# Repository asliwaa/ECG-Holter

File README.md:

# ECG Holter with MQTT Streaming

A portable ECG recorder that streams the signal in real time over Wi-Fi to a server using the MQTT protocol. The recorded signal is visualized live in a web dashboard.

Developed as an engineering thesis project in Computer Science at the Faculty of Automatic Control, Electronics and Computer Science, Silesian University of Technology (Politechnika Śląska).

---

## Table of contents

- [How it works](#how-it-works)
- [Hardware](#hardware)
- [Software](#software)
- [Repository structure](#repository-structure)
- [Project status](#project-status)
- [Safety](#safety)
- [License](#license)

---

## How it works

```mermaid
flowchart LR
    E[ECG electrodes] --> A[AD8232<br/>analog front-end]
    A -->|analog signal| M[ESP32-S3<br/>ADC, filtering, R-peak detection]
    M -->|Wi-Fi, MQTT| B[(Broker<br/>Mosquitto)]
    B -->|MQTT over WebSocket| D[Web dashboard<br/>live chart, BPM]
    P[Li-Po battery<br/>+ USB-C charging] -.-> M
    P -.-> A
```

1. The **AD8232** module amplifies and pre-filters the signal from the electrodes.
2. The **ESP32-S3** samples the signal with its ADC, applies digital filtering (high-pass and 50 Hz notch), detects R-peaks and calculates the heart rate.
3. Samples are sent in batches over **MQTT** to a Mosquitto broker.
4. The **web dashboard** subscribes to the data via MQTT over WebSocket and draws the ECG waveform live.

## Hardware

Custom PCB designed in KiCad 10, powered by a Li-Po battery.

| Block | Components | Function |
|---|---|---|
| USB-C input | GCT USB4105, USBLC6-2SC6 | Charging and programming, ESD protection |
| Charging | MCP73831 | Li-Po charging at 500 mA (CC/CV, 4.2 V) |
| Power path | AO3401A, SS14 | Automatic source selection: USB or battery |
| Regulator | AP2112K-3.3 | 3.3 V supply (up to 600 mA) |
| Microcontroller | ESP32-S3-WROOM-1-N8 | Acquisition, processing, Wi-Fi |
| ECG front-end | AD8232 module | ECG signal amplification and filtering, lead-off detection |
| Monitoring | Voltage dividers | Battery level, USB connection detection |

## Software

| Part | Technology |
|---|---|
| Firmware | ESP32-S3, Arduino / PlatformIO |
| Transport | MQTT |
| Broker | Mosquitto (with WebSocket support) |
| Dashboard | HTML / JavaScript, mqtt.js, real-time chart |

## Repository structure

```
├── hardware/        # KiCad project: schematic, PCB, libraries, fabrication files
├── firmware/        # ESP32-S3 firmware
├── server/          # Mosquitto broker configuration
├── dashboard/       # web dashboard
└── docs/            # documentation, photos, measurement results
```

## Project status

- [x] Concept and component selection
- [ ] Schematic (in progress)
- [ ] PCB layout and board order
- [ ] Breadboard prototype: ECG sampling
- [ ] MQTT streaming
- [ ] Web dashboard with live chart
- [ ] Bring-up of the custom PCB
- [ ] Digital filtering and heart rate detection
- [ ] Tests: latency, packet loss, battery life

## Safety

> [!WARNING]
> This is an educational prototype, **not a medical device**. It is not intended for diagnosis or health monitoring.
>
> When electrodes are attached to the body, the device must be powered **from the battery only**. Never attach electrodes while the board is connected via USB to a computer or a mains-powered charger. The firmware disables ECG acquisition when USB voltage is detected.

## License

- Software (`firmware/`, `server/`, `dashboard/`): [MIT](LICENSE)
- Hardware design (`hardware/`): [CERN-OHL-S-2.0](hardware/LICENSE)

## Author

Adam Śliwa · Engineering thesis

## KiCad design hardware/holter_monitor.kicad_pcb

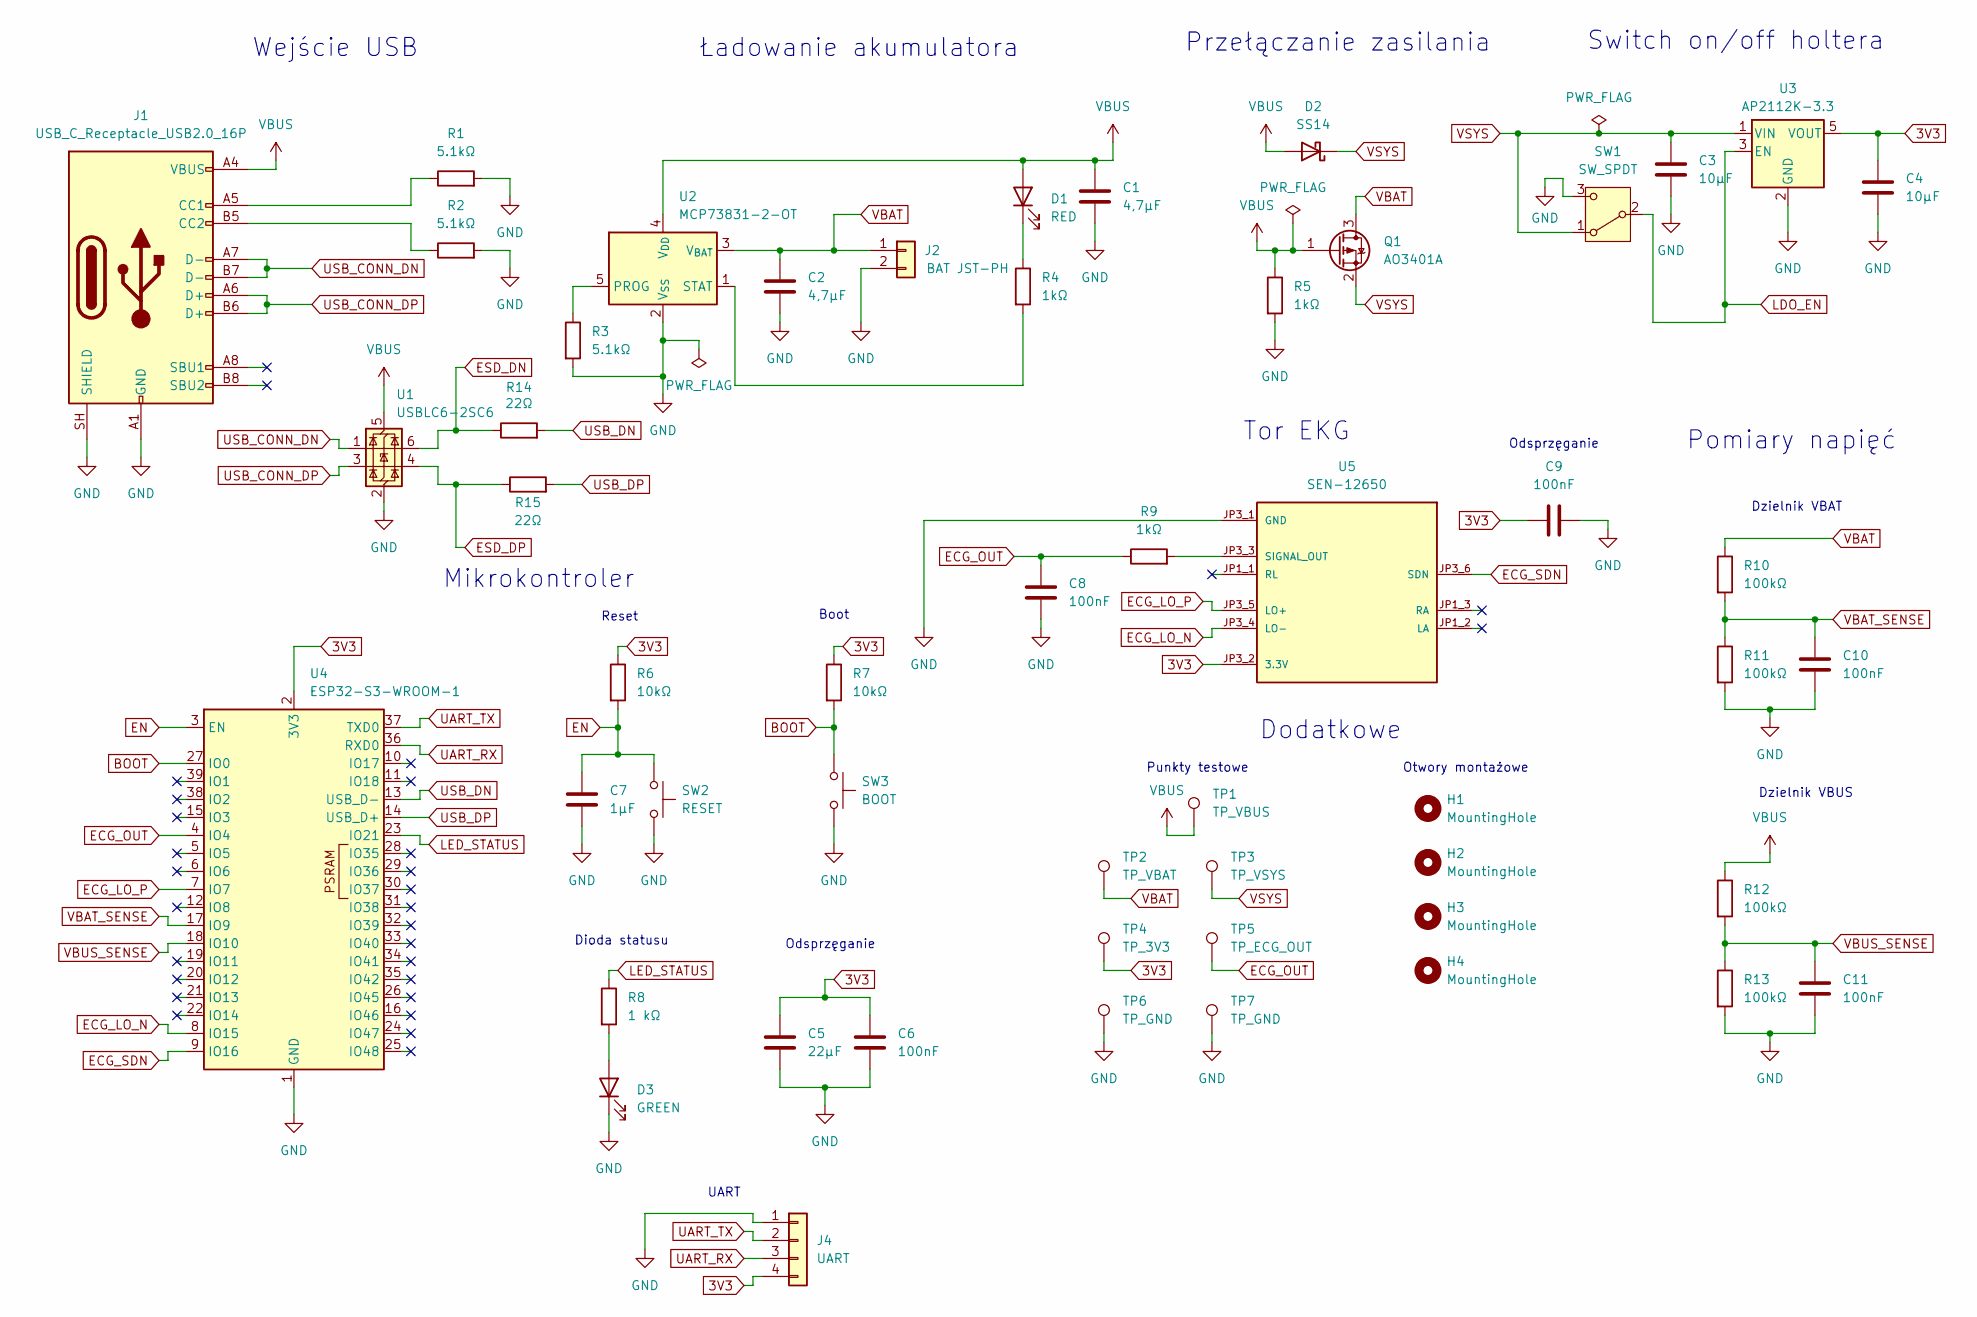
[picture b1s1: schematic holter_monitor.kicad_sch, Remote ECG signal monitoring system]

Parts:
C1, C2: 4,7µF; C_0805_2012Metric_Pad1.18x1.45mm_HandSolder
C3, C4: 10µF; C_0805_2012Metric_Pad1.18x1.45mm_HandSolder
C5: 22µF; C_0805_2012Metric_Pad1.18x1.45mm_HandSolder
C6, C8, C9, C10, C11: 100nF; C_0805_2012Metric_Pad1.18x1.45mm_HandSolder
C7: 1µF; C_0805_2012Metric_Pad1.18x1.45mm_HandSolder
D1: RED; LED_0805_2012Metric_Pad1.15x1.40mm_HandSolder
D2: SS14; D_SMA_Handsoldering
D3: GREEN; LED_0805_2012Metric_Pad1.15x1.40mm_HandSolder
H1, H2, H3, H4: MountingHole; MountingHole_3.2mm_M3
J1: USB_C_Receptacle_USB2.0_16P; USB_C_Receptacle_GCT_USB4105-xx-A_16P_TopMnt_Horizontal
J2: BAT JST-PH; JST_PH_S2B-PH-K_1x02_P2.00mm_Horizontal
J4: UART; PinHeader_1x04_P2.54mm_Vertical
Q1: AO3401A; SOT-23_Handsoldering
R1, R2, R3: 5.1kΩ; R_0805_2012Metric_Pad1.20x1.40mm_HandSolder
R4, R5, R9: 1kΩ; R_0805_2012Metric_Pad1.20x1.40mm_HandSolder
R6, R7: 10kΩ; R_0805_2012Metric_Pad1.20x1.40mm_HandSolder
R8: 1 kΩ; R_0805_2012Metric_Pad1.20x1.40mm_HandSolder
R10, R11, R12, R13: 100kΩ; R_0805_2012Metric_Pad1.20x1.40mm_HandSolder
R14, R15: 22Ω; R_0805_2012Metric_Pad1.20x1.40mm_HandSolder
SW1: SW_SPDT; SW_Slide_SPDT_Straight_CK_OS102011MS2Q
SW2: RESET; SW_SPST_TL3342
SW3: BOOT; SW_SPST_TL3342
TP1: TP_VBUS; TestPoint_Pad_D1.5mm
TP2: TP_VBAT; TestPoint_Pad_D1.5mm
TP3: TP_VSYS; TestPoint_Pad_D1.5mm
TP4: TP_3V3; TestPoint_Pad_D1.5mm
TP5: TP_ECG_OUT; TestPoint_Pad_D1.5mm
TP6, TP7: TP_GND; TestPoint_Pad_D1.5mm
U1: USBLC6-2SC6; SOT-23-6_Handsoldering
U2: MCP73831-2-OT; SOT-23-5_HandSoldering
U3: AP2112K-3.3; SOT-23-5_HandSoldering
U4: ESP32-S3-WROOM-1
U5: SEN-12650; MODULE_SEN-12650; PARTREV V10

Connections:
3V3: C4.1, C5.1, C6.1, C9.1, J4.4, R6.1, R7.1, TP4.1 (1_1), U3.5 (VOUT), U4.2 (3V3), U5.JP3_2 (3.3V)
BOOT: R7.2, SW3.1, U4.27 (IO0)
ECG_LO_N: U4.8 (IO15), U5.JP3_4 (LO-)
ECG_LO_P: U4.7 (IO7), U5.JP3_5 (LO+)
ECG_OUT: C8.1, R9.1, TP5.1 (1_1), U4.4 (IO4)
ECG_SDN: U4.9 (IO16), U5.JP3_6 (SDN)
EN: C7.1, R6.2, SW2.1, U4.3 (EN)
ESD_DN: R14.1, U1.6 (I/O1)
ESD_DP: R15.1, U1.4 (I/O2)
GND: C1.2, C2.2, C3.2, C4.2, C5.2, C6.2, C7.2, C8.2, C9.2, C10.2, C11.2, D3.1 (K), J1.A1 (GND), J1.A12 (GND), J1.B1 (GND), J1.B12 (GND), J1.SH (SHIELD), J2.2, J4.1, R1.2, R2.2, R3.2, R5.2, R11.2, R13.2, SW1.3 (C), SW2.2, SW3.2, TP6.1 (1_1), TP7.1 (1_1), U1.2 (GND), U2.2 (V_{SS}), U3.2 (GND), U4.1 (GND), U4.40 (GND), U4.41 (GND), U5.JP3_1 (GND)
LDO_EN: SW1.2 (B), U3.3 (EN)
LED_STATUS: R8.1, U4.23 (IO21)
unnamed: D1.1 (K), R4.1
unnamed: D3.2 (A), R8.2
unnamed: J1.A5 (CC1), R1.1
unnamed: J1.B5 (CC2), R2.1
unnamed: R3.1, U2.5 (PROG)
unnamed: R4.2, U2.1 (STAT)
unnamed: R9.2, U5.JP3_3 (SIGNAL_OUT)
UART_RX: J4.3, U4.36 (RXD0)
UART_TX: J4.2, U4.37 (TXD0)
USB_CONN_DN: J1.A7 (D-), J1.B7 (D-), U1.1 (I/O1)
USB_CONN_DP: J1.A6 (D+), J1.B6 (D+), U1.3 (I/O2)
USB_DN: R14.2, U4.13 (USB_D-)
USB_DP: R15.2, U4.14 (USB_D+)
VBAT: C2.1, J2.1, Q1.3 (D), R10.1, TP2.1 (1_1), U2.3 (V_{BAT})
VBAT_SENSE: C10.1, R10.2, R11.1, U4.17 (IO9)
VBUS: C1.1, D1.2 (A), D2.2 (A), J1.A4 (VBUS), J1.A9 (VBUS), J1.B4 (VBUS), J1.B9 (VBUS), Q1.1 (G), R5.1, R12.1, TP1.1 (1_1), U1.5 (VBUS), U2.4 (V_{DD})
VBUS_SENSE: C11.1, R12.2, R13.1, U4.18 (IO10)
VSYS: C3.1, D2.1 (K), Q1.2 (S), SW1.1 (A), TP3.1 (1_1), U3.1 (VIN)

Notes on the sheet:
Dzielnik VBAT
Boot
Reset
Odsprzęganie
Switch on/off holtera
UART
Przełączanie zasilania
Wejście USB
Dzielnik VBUS
Dioda statusu
Punkty testowe
Pomiary napięć
Ładowanie akumulatora
Dodatkowe
Otwory montażowe
Mikrokontroler
Tor EKG

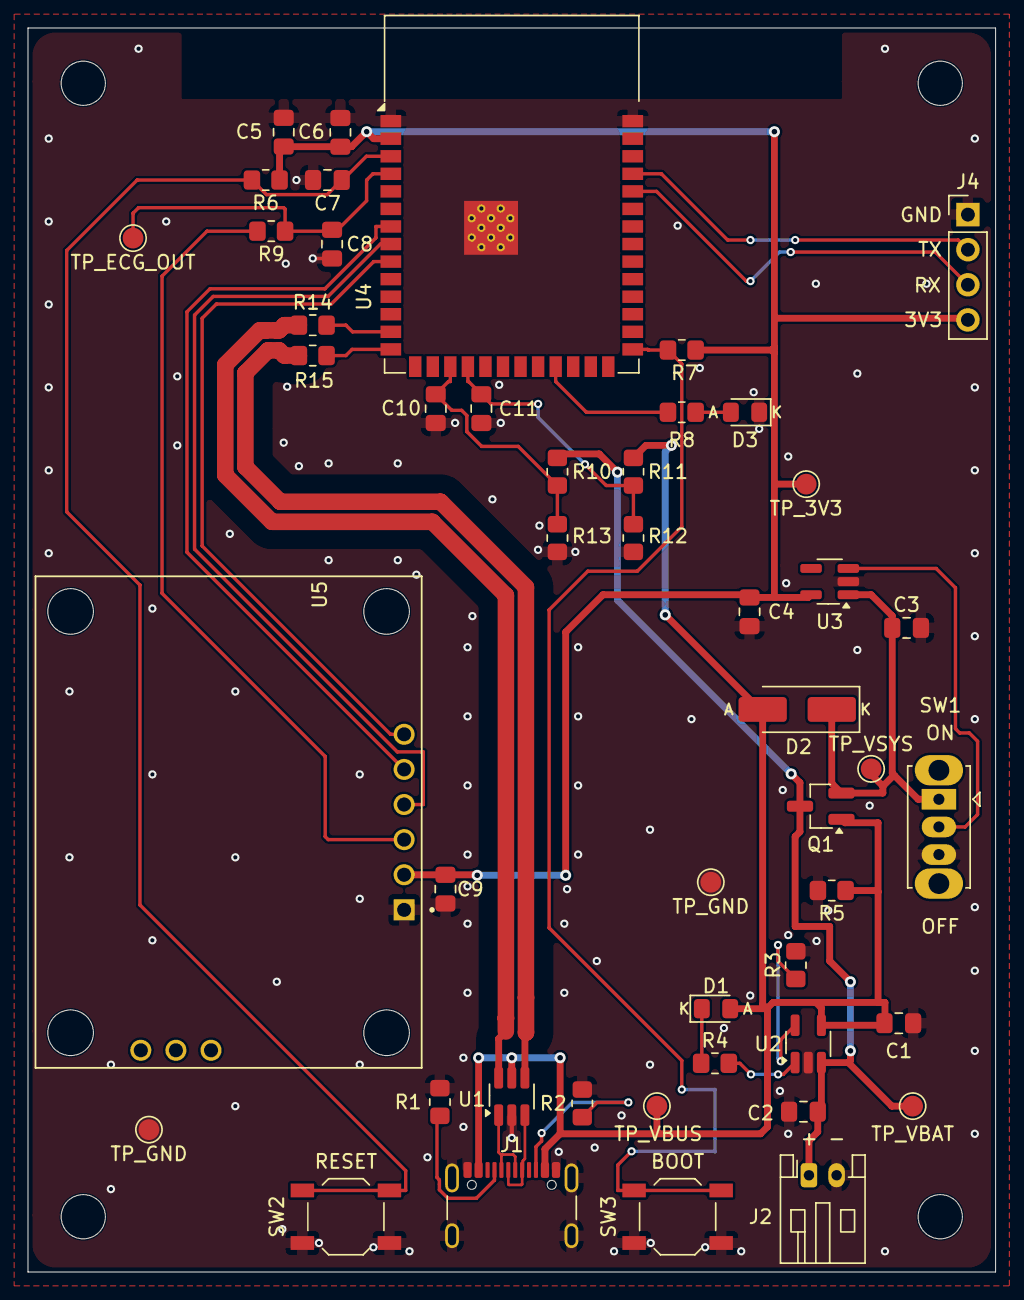
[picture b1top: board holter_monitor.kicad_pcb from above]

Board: 2 copper layers, 70.0 x 90.0 mm, 52 parts (0 on the bottom side), 30 nets.

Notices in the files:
README.md:
License: MIT / CERN-OHL-S
